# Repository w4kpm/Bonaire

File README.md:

# Bonaire Envronmental Sensor

Particulate Sensor / Pressure /Humidity /VOC sensor

24v / Modbus - inital modbusid = 65 baud = 9600

uses low cost BME680 for pressure, humidity, temp and voc
it also uses 2x pms5003 to measure particulate matter

details about the parameters are in the PDF's of the individual sensors

RS-485 and 24v are hooked up by 1 M12 connector 

modbus registers:

   1: pressure
    
   2: humidity
    
   3: a_pm1_0_atm
    
   4: a_pm2_5_atm
    
   5: a_pm10_0_atm
    
   6: a_pm1_0_cf_1
    
   7: a_pm2_5_cf_1
    
   8: a_pm10_0_cf_1
    
   9: a_p_0_3_um
   
   10: a_p_0_5_um
   
   11: a_p_1_0_um
   
   12: a_p_2_5_um
   
   13: a_p_5_0_um
   
   14: a_p_10_0_um
   
   15: b_pm1_0_atm
   
   16: b_pm2_5_atm
   
   17: b_pm10_0_atm
   
   18: b_pm1_0_cf_1
   
   19: b_pm2_5_cf_1
   
   20: b_pm10_0_cf_1
   
   21: b_p_0_3_um
   
   22: b_p_0_5_um
   
   23: b_p_1_0_um
   
   24: b_p_2_5_um
   
   25: b_p_5_0_um
   
   26: b_p_10_0_um
   
   27: voc
   
   28: temp

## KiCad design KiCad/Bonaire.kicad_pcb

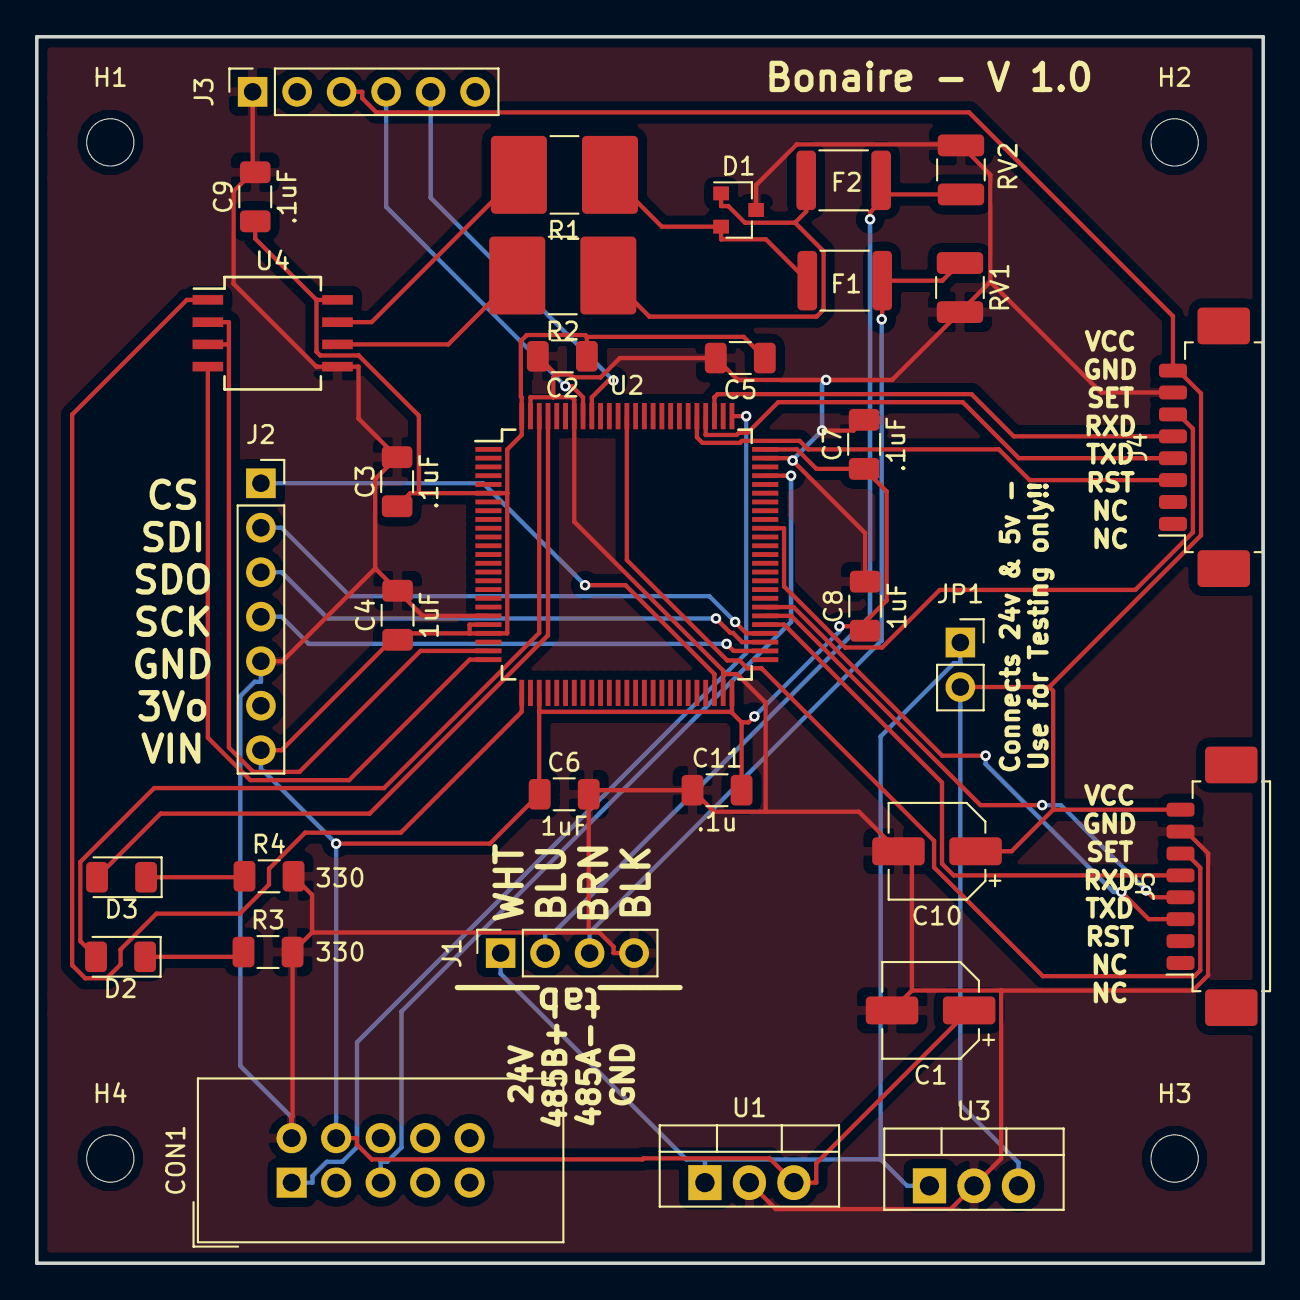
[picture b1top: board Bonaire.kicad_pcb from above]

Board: 2 copper layers, 70.0 x 70.0 mm, 37 parts (0 on the bottom side), 33 nets.

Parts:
C1, C10: 100uF; CP_Elec_5x5.3
C2, C4, C6, C8: 1uF; C_1206_3216Metric
C3, C5, C7, C9: .1uF; C_1206_3216Metric
C11: .1u; C_1206_3216Metric
CON1: AVR-JTAG-10; IDC-Header_2x05_P2.54mm_Vertical
D1: D_TVS_x2_AAC; SOT-23
D2, D3: LED; LED_1206_3216Metric
F1, F2: Polyfuse_Small; R_1812_4532Metric
H1, H2, H3, H4: MountingHole; MountingHole_2.7mm_M2.5
J1: Conn_01x04; PinSocket_1x04_P2.54mm_Vertical
J2: Conn_01x07; PinSocket_1x07_P2.54mm_Vertical
J3: Conn_01x06; PinSocket_1x06_P2.54mm_Vertical
J4, J5: Conn_01x08; Molex_PicoBlade_53261-0871_1x08-1MP_P1.25mm_Horizontal
JP1: Jumper; PinSocket_1x02_P2.54mm_Vertical
R1, R2: 10; R_2816_7142Metric_Pad3.20x4.45mm_HandSolder
R3, R4: 330; R_1206_3216Metric
RV1, RV2: Varistor; R_1210_3225Metric
U1: LM78l33_TO220; TO-220-3_Vertical
U2: STM32F303V(B-C)Tx_u; LQFP-100_14x14mm_P0.5mm
U3: LM78l50_TO220; TO-220-3_Vertical
U4: SN65HV7X; SO-8_5.3x6.2mm_P1.27mm

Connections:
+3V3: C1.1, C2.1, C3.1, C4.1, C5.1, C6.1, C7.1, C8.1, C9.1, C11.2, CON1.4, J2.7, U1.3, U2.6, U2.21, U2.22, U2.28, U2.50, U2.75, U2.100, U4.8
+5V: C10.1, J3.3, J4.8, J5.8, JP1.2, U3.3
+24V: J1.1, JP1.1, U1.1, U3.1
/GPIOA/serial/RX: U2.26, U4.1
/GPIOA/serial/TX: U2.25, U4.4
/GPIOA/serial/TX_en: U2.24, U4.2, U4.3
/GPIOB/MISO: J2.3, U2.53
/GPIOB/MOSI: J2.2, U2.54
/GPIOB/SCK: J2.4, U2.52
/GPIOB/UART1_RX: J3.4, U2.93
/GPIOB/UART1_TX: J3.5, U2.92
/GPIOB/~CS: J2.1, U2.48
/RS485A: F2.1, J1.2, RV2.1
/RS485B: F1.1, J1.3, RV1.1
GND: C1.2, C2.2, C3.2, C4.2, C5.2, C6.2, C7.2, C8.2, C9.2, C10.2, C11.1, CON1.2, D1.3, J1.4, J2.5, J3.1, J4.7, J5.7, R3.2, R4.2, RV1.2, RV2.2, U1.2, U2.20, U2.49, U2.74, U2.94, U2.99, U3.2, U4.5
unnamed: CON1.1, U2.76
unnamed: CON1.5, U2.72
unnamed: D1.1, F2.2, R2.1
unnamed: D1.2, F1.2, R1.1
unnamed: D2.1, R3.1
unnamed: D2.2, U2.98
unnamed: D3.1, R4.1
unnamed: D3.2, U2.97
unnamed: J4.3, U2.80
unnamed: J4.4, U2.79
unnamed: J4.5, U2.78
unnamed: J4.6, U2.66
unnamed: J5.3, U2.57
unnamed: J5.4, U2.56
unnamed: J5.5, U2.55
unnamed: J5.6, U2.88
unnamed: R1.2, U4.7
unnamed: R2.2, U4.6

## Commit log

2019-06-24 initial add - stolen from Helios
2019-06-24 remove all build folders
2019-06-24 Reading the first particulate sensor
2019-07-01 Added Board code to repository
2019-07-01 add extra kicad directory
2019-07-01 revised Schematic for Beta version of Bonaire
2019-07-01 Have board layout done, need to route
2019-07-08 Add Last send of Circuit board
2019-07-08 start to read config parameters from BME680
2019-07-18 Make changes to circuit boardq
2019-07-18 make sure board is updated
2019-07-22 got BME Sensor Working
2019-07-22 BME 680 and particulate sensor now.
2019-07-29 final code
2019-07-29 add G-code for cutting boxes
2020-08-04 final commit
2021-03-17 Add basic modbus information
    Add all of the registers that are able to be read.
2021-03-17 Add note about connector
